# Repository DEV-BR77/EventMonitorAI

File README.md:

# EventMonitorAI

> **Lokale, datenschutzorientierte Plattform zur Erfassung, Analyse und lernenden Klassifizierung akustischer Ereignisse.**

EventMonitorAI verbindet ESP32-Audiosensoren, Raspberry-Pi-Edge-Verarbeitung, eine FastAPI-Ereignisplattform und **EventMonitor AudioLab** für historische Messungen. Ziel ist, große Mengen vorhandener und künftiger Lärmaufnahmen automatisch zu strukturieren, auffällige Abschnitte zu finden und durch bestätigte Zuordnungen schrittweise eine an die reale Umgebung angepasste Erkennung aufzubauen.

## Projektstatus

**Entwicklungsphase:** v1.0-Kandidat / Abnahme und Langzeittest

Aktuell vorhanden:

- ESP32-S3-Audiosender per UDP
- Raspberry-Pi-Empfänger mit YAMNet-basierter Klassifizierung
- FastAPI-Backend mit SQLite-Ereignisdatenbank
- REST-Endpunkte für Health-Check und Ereignisse
- geschütztes Dashboard mit Kalender, Timeline, Heatmap, Statistiken und Live-Ansicht
- lokale Benutzerrollen, Mehrgerätebetrieb, Live-Sound-Freigaben, installierbare PWA und Push-Benachrichtigungen
- Home-Assistant-Webhook und optionale PostgreSQL-Datenbank
- deutsche Label- und Kategoriezuordnung
- EventMonitor AudioLab für ZIP-Massenimport, Segmentierung, Anhören, Labeling und CSV-Export

Die Funktionen bis Phase 9 sind implementiert. Ein v1.0-Tag wird erst nach dem
dokumentierten 24-Stunden-Langzeittest, Restore-Test auf einer getrennten
Datenbank und der Betreiber-/Datenschutzfreigabe erstellt.

## Schwerpunkt der Erkennung

Das System wird zunächst für folgende akustische Klassen optimiert:

- Schreien und lautes Rufen
- Streit oder mehrere laute Stimmen
- Schlagen, Klopfen und andere Aufprallgeräusche
- Türknallen
- Auto und Vorbeifahrt
- Motorrad
- Hupe

Zusätzliche Negativ- und Kontextklassen wie normales Sprechen, Hund, Musik, Maschinen, Wind oder Regen reduzieren Fehlalarme.

> EventMonitorAI erkennt akustische Muster. Es stellt nicht zweifelsfrei fest, welche Person oder Ursache ein Geräusch erzeugt hat. Automatische Ergebnisse bleiben Vorschläge, bis sie bestätigt wurden.

## Systemübersicht

```text
ESP32-S3 + INMP441
        │ UDP-Audio
        ▼
Raspberry Pi / Edge Receiver
        │ Ereignisse + Pegel + Modellresultate + flüchtiger Live-Audiostream
        ▼
FastAPI Backend ───────────────► SQLite / später PostgreSQL
        │
        ├── REST API und geschütztes Dashboard
        ├── Live- und Ereignisdaten
        └── PostgreSQL, automatische Backups und Clips

Historische ZIP-/Audio-Messungen
        │
        ▼
EventMonitor AudioLab
        ├── Massenimport und Dublettenprüfung
        ├── dB-/Audio-Segmentierung
        ├── Human-in-the-Loop-Labeling
        └── Trainings- und Lärmprotokoll-Daten
```

Detaillierte Beschreibung: [docs/Architecture.md](docs/Architecture.md)

## Repository-Struktur

```text
EventMonitorAI/
├── .github/                 GitHub-Workflows und Vorlagen
├── backend/                 FastAPI-Backend und Datenmodell
├── edge/raspberry-pi/       Edge-Empfänger und lokale Klassifizierung
├── firmware/                ESP32-S3-Firmware
├── tools/audio-lab/         Historischer Import und Lernoberfläche
├── docs/                    Architektur, Betrieb, Entwicklung und Roadmap
├── tests/                   automatisierte Tests
├── scripts/                 Entwickler- und Prüfskripte
├── models/                  lokale Modellablage, Inhalte nicht versioniert
├── exports/                 lokale Exporte, Inhalte nicht versioniert
└── logs/                    lokale Logs, Inhalte nicht versioniert
```

## Schnellstart: Backend

Voraussetzungen: Python 3.11 oder neuer.

```powershell
cd backend
py -m venv .venv
.\.venv\Scripts\Activate.ps1
python -m pip install --upgrade pip
pip install -r requirements.txt
Copy-Item .env.example .env
uvicorn app.main:app --reload
```

Danach:

- API-Dokumentation: `http://127.0.0.1:8000/docs`
- Health-Check: `http://127.0.0.1:8000/health`
- Dashboard: `http://127.0.0.1:8000/`

Ausführliche Anleitung: [docs/getting-started/INSTALLATION.md](docs/getting-started/INSTALLATION.md)

## Schnellstart: EventMonitor AudioLab

```powershell
cd tools\audio-lab
.\start_windows.bat
```

AudioLab öffnet eine lokale Browseroberfläche für Import, Wiedergabe, Labeling und Auswertung. Details: [tools/audio-lab/README.md](tools/audio-lab/README.md)

## Entwicklung

Vor Änderungen bitte lesen:

- [CONTRIBUTING.md](CONTRIBUTING.md)
- [docs/development/CODING_GUIDELINES.md](docs/development/CODING_GUIDELINES.md)
- [docs/development/BRANCHING_AND_RELEASES.md](docs/development/BRANCHING_AND_RELEASES.md)
- [SECURITY.md](SECURITY.md)

Lokale Qualitätsprüfung:

```powershell
py scripts/check_project.py
```

Die GitHub-CI prüft Python-Syntax, Tests, sensible Dateien und grundlegende Repository-Hygiene.

## Dokumentation

| Thema | Dokument |
|---|---|
| Installation | [docs/getting-started/INSTALLATION.md](docs/getting-started/INSTALLATION.md) |
| Architektur | [docs/Architecture.md](docs/Architecture.md) |
| Dashboard und Integrationen | [docs/PHASE5_DASHBOARD.md](docs/PHASE5_DASHBOARD.md) |
| Zweistufige KI-Klassifikation | [docs/PHASE7_KI.md](docs/PHASE7_KI.md) |
| AudioLab | [tools/audio-lab/README.md](tools/audio-lab/README.md) |
| Roadmap | [docs/Roadmap.md](docs/Roadmap.md) |
| Produkt-Backlog | [docs/ProductBacklog.md](docs/ProductBacklog.md) |
| Entscheidungen | [docs/DecisionLog.md](docs/DecisionLog.md) und [docs/adr/](docs/adr/) |
| Betrieb und Datenschutz | [docs/operations/PRIVACY_AND_DATA.md](docs/operations/PRIVACY_AND_DATA.md) |
| Installation und Upgrade | [docs/operations/INSTALL_UPGRADE.md](docs/operations/INSTALL_UPGRADE.md) |
| Backup und Restore | [docs/operations/BACKUP_RESTORE.md](docs/operations/BACKUP_RESTORE.md) |
| Performance | [docs/operations/PERFORMANCE.md](docs/operations/PERFORMANCE.md) |
| Security-Review | [docs/operations/SECURITY_PRIVACY_REVIEW.md](docs/operations/SECURITY_PRIVACY_REVIEW.md) |
| v1.0-Kriterien | [docs/releases/V1_RELEASE_CRITERIA.md](docs/releases/V1_RELEASE_CRITERIA.md) |

## Leitprinzipien

1. **Privacy first** – lokale Verarbeitung und Datenkontrolle.
2. **Local first** – Kernfunktionen ohne Cloud-Zwang.
3. **Everything is an event** – ein gemeinsames Ereignismodell.
4. **Human in the loop** – bestätigte Labels statt blindem Selbstlernen.
5. **Simple before clever** – nachvollziehbare, testbare Schritte.
6. **Documentation matters** – Architektur und Entscheidungen werden dokumentiert.
7. **Quality over speed** – stabile Daten und reproduzierbare Ergebnisse.

## Lizenz

Siehe [LICENSE](LICENSE).

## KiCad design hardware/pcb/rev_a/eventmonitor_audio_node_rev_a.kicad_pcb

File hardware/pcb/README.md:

# JLCPCB-Kalkulationspakete

`generated/carrier/eventmonitor_audio_carrier-JLCPCB.zip` ist ein zweilagiger,
gerouteter Rev-A-Prototyp fuer das Freenove ESP32-S3 N16R8 Board und einen
INMP441-Stecksockel. Vor Bestellung sind die tatsaechlichen Header-Mittelpunkte
und die Pinreihenfolge des gekauften Mikrofons mit dem Messschieber zu pruefen.

Die beiden SMD-Verzeichnisse sind Preisvorlagen mit finaler Umrissgroesse, BOM und
CPL-Schema. Sie sind **nicht** als Fertigungsfreigabe gedacht: USB-C, ESD,
Stromversorgung, Antennen-Freihaltezone sowie bei LiPo die Schutz- und
Ladeschaltung werden erst nach Auswahl des konkreten Akkus final geroutet.

## Native-USB-SMD-Platine mit externer Antenne (Kalkulation)

`generated/smd_native_usb_external_antenna_quote/` enthält die aktuelle
Kalkulationsmappe ohne Steckfassungen:

- `smd_native_usb_external_antenna_quote-JLCPCB.zip` – Gerberarchiv für den
  PCB-Preisrechner;
- `BOM.csv` – Stückliste einschließlich Montagehinweisen;
- `CPL.csv` – Bestückungskoordinaten für JLCPCB;
- `board-preview.png` – reine Sichtprüfung der Bauteilplatzierung.

Die Platine ist 65 × 50 mm groß und enthält das externe-Antennenmodul
`ESP32-S3-WROOM-1U-N16R8`, einen direkt aufgelöteten ICS-43434-I²S-MEMS-Sensor,
USB-C für 5 V und natives USB (GPIO19/GPIO20), AMS1117-3.3, BOOT/RESET,
Status-LED und vier M2.5-Gehäusebohrungen. Das RP-SMA-Teil ist bewusst kein
Platinenbauteil: Es ist ein U.FL-auf-RP-SMA-Bulkhead-Pigtail, das direkt an die
bereits vorhandene U.FL-Buchse des WROOM-1U-Moduls kommt und später im Gehäuse
verschraubt wird.

Wichtig: `ESP32-S3-WROOM-1-N16R8-H4` ist keine einzelne Espressif-Variante.
`N16R8` (16 MB Flash, 8 MB PSRAM) und `H4` sind unterschiedliche
Speicher-/Temperaturvarianten. Für die gewünschte RP-SMA-Antenne ist die
`1U`-Variante erforderlich. Diese Mappe ist absichtlich als **QUOTE ONLY –
NOT FOR MANUFACTURING** angelegt: Vor einer Fertigungsfreigabe fehlen noch
Schaltplan/Netzliste, USB-ESD-Schutz, vierlagiges Impedanz- und RF-Routing,
Mikrofon-Akustiköffnung sowie DRC/ERC und ein Musteraufbau.

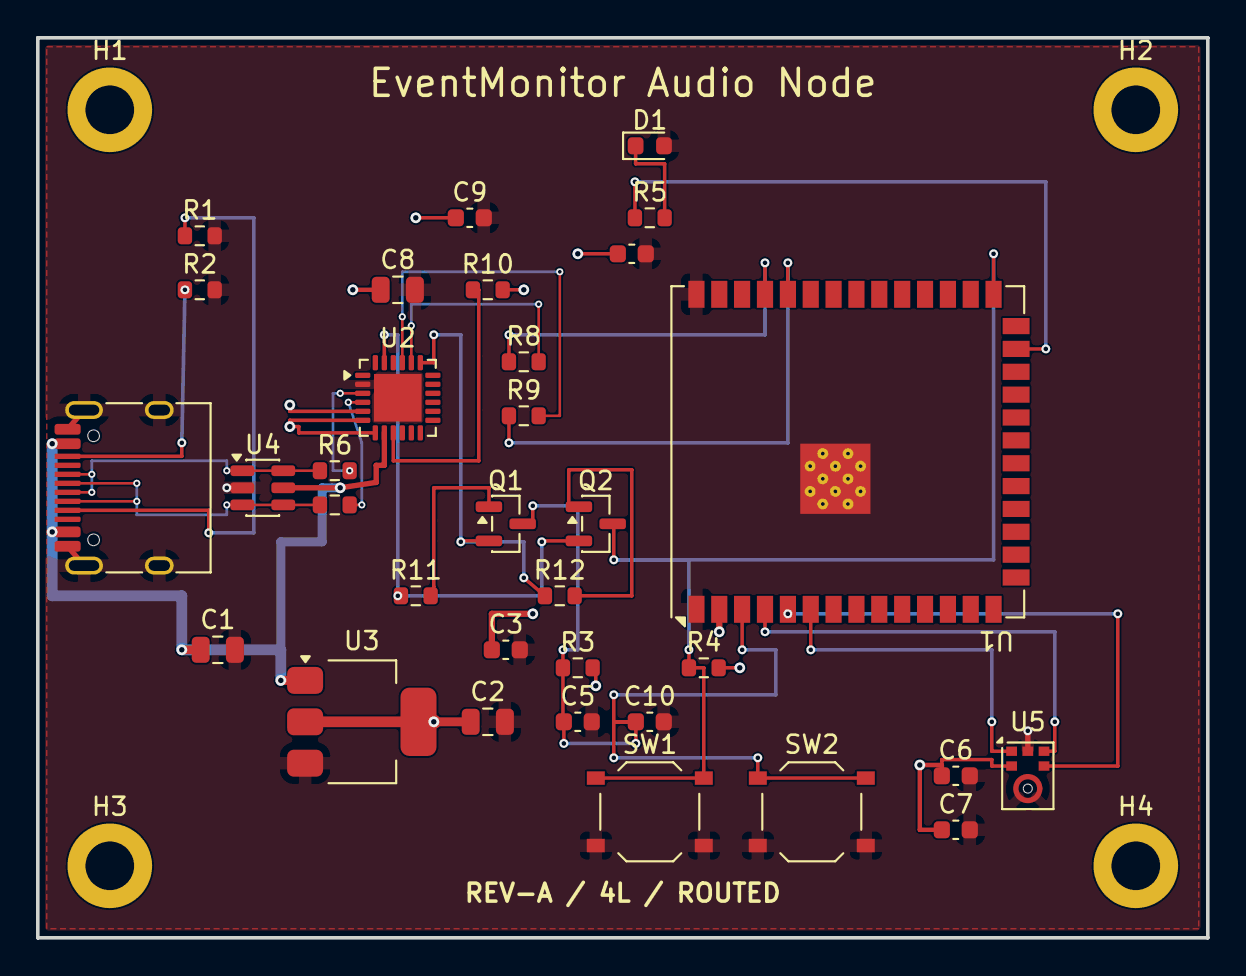
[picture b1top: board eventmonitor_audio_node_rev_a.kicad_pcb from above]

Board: 4 copper layers, 65.0 x 50.0 mm, 37 parts (0 on the bottom side), 25 nets.

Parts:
C1: 10u VIN; C_0805_2012Metric
C2: 10u VOUT; C_0805_2012Metric
C3: 100n U3; C_0603_1608Metric
C4: 100n U1; C_0603_1608Metric
C5: 100n EN; C_0603_1608Metric
C6: 1u MIC; C_0603_1608Metric
C7: 100n MIC; C_0603_1608Metric
C8: 4u7 U2; C_0805_2012Metric
C9: 100n U2; C_0603_1608Metric
C10: 1u EN; C_0603_1608Metric
D1: GREEN; LED_0603_1608Metric
H1, H2, H3, H4: M2.5; MountingHole_2.7mm_M2.5_DIN965_Pad
J1: USB-C USB2.0; USB_C_Receptacle_HRO_TYPE-C-31-M-12
Q1, Q2: BC847B; SOT-23
R1, R2: 5.1k; R_0603_1608Metric
R3: 10k EN; R_0603_1608Metric
R4: 10k BOOT; R_0603_1608Metric
R5: 1k LED; R_0603_1608Metric
R6: 22R D+; R_0603_1608Metric
R7: 22R D-; R_0603_1608Metric
R8: 499R TX; R_0603_1608Metric
R9: 499R RX; R_0603_1608Metric
R10: 1k U2 RST; R_0603_1608Metric
R11: 10k DTR; R_0603_1608Metric
R12: 10k RTS; R_0603_1608Metric
SW1: BOOT; SW_Push_1P1T_XKB_TS-1187A
SW2: RESET; SW_Push_1P1T_XKB_TS-1187A
U1: ESP32-S3-WROOM-1U-N16R8; ESP32-S3-WROOM-1U
U2: CP2102N-A02-GQFN24R; QFN-24-1EP_4x4mm_P0.5mm_EP2.65x2.65mm
U3: AMS1117-3.3; SOT-223-3_TabPin2
U4: USBLC6-2SC6; SOT-23-6
U5: ICS-43434; InvenSense_ICS-43434-6_3.5x2.65mm

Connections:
+3V3: C2.1, C3.1, C4.1, C6.1, C7.1, C8.1, C9.1, R3.2, R4.2, R10.2, U1.2, U2.5, U2.6, U2.7, U3.2, U5.2
AUTO_DTR: Q2.2, R11.1, U2.23
AUTO_RTS: Q1.2, R12.1, U2.19
BOOT: Q2.3, R4.1, SW1.1, U1.27
EN: C5.1, C10.1, Q1.3, R3.1, SW2.1, U1.3
GND: C1.2, C2.2, C3.2, C4.2, C5.2, C6.2, C7.2, C8.2, C9.2, C10.2, D1.2, J1.A1, J1.A12, J1.B1, J1.B12, J1.SH, R1.2, R2.2, SW1.2, SW2.2, U1.1, U1.40, U1.41, U2.2, U2.25, U3.3, U4.2, U5.3, U5.6
I2S_BCLK: U1.5, U5.4
I2S_DATA: U1.6, U5.1
I2S_WS: U1.4, U5.5
LED_A: D1.1, R5.2
LED_STATUS: R5.1, U1.25
Q1_BASE: Q1.1, R11.2
Q2_BASE: Q2.1, R12.2
U2_RST: R10.1, U2.9
UART_RX_CP: R8.2, U2.20
UART_RX_ESP: R9.1, U1.36
UART_TX_CP: R9.2, U2.21
UART_TX_ESP: R8.1, U1.37
USB_5V: C1.1, J1.A4, J1.A9, J1.B4, J1.B9, U2.8, U3.1, U4.5
USB_CC1: J1.A5, R1.1
USB_CC2: J1.B5, R2.1
USB_D+: R6.2, U2.3
USB_D+_ESD: J1.A6, J1.B6, R6.1, U4.1, U4.6
USB_D-: R7.2, U2.4
USB_D-_ESD: J1.A7, J1.B7, R7.1, U4.3, U4.4

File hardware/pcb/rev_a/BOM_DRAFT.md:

# Rev-A preliminary BOM

| References | Part / value | Package | Role |
| --- | --- | --- | --- |
| U1 | ESP32-S3-WROOM-1U-N16R8 | module | MCU and external U.FL antenna connector |
| U2 | CP2102N-A02-GQFN24R (`C969151`) | QFN-24-EP 4×4 mm | USB-to-UART programming bridge; includes DTR and RTS for standard auto-programming |
| U3 | AMS1117-3.3 | SOT-223-3 | 5 V to 3.3 V regulator |
| U4 | USBLC6-2SC6 | SOT-23-6 | USB ESD protection |
| U5 | ICS-43434 | LGA-6 | bottom-port I²S microphone |
| J1 | USB-C USB2.0 receptacle | 16-pin SMD | power and data |
| SW1 / SW2 | SMD tactile switch | 3×4 mm | BOOT / RESET |
| Q1 / Q2 | BC847B | SOT-23 | auto-programming pair |
| D1 | green LED | 0603 | status output |
| R1 / R2 | 5.1 kΩ 1% | 0603 | USB-C CC pull-downs |
| R3 / R4 | 10 kΩ 1% | 0603 | EN and GPIO0 pull-ups |
| R5 | 1 kΩ | 0603 | LED resistor |
| R6 / R7 | 22 Ω | 0603 | optional USB damping |
| R8 / R9 | 499 Ω | 0603 | UART series resistors |
| R11 / R12 | 10 kΩ 1% | 0603 | DTR/RTS auto-program base resistors |
| R10 | 1 kΩ | 0603 | CP2102N reset pull-up |
| C1 | 10 µF 10 V X5R | 0805 | AMS1117 input |
| C2 | 10 µF 6.3 V X5R | 0805 | AMS1117 output |
| C3 / C4 | 100 nF X7R | 0603 | regulator / MCU bypass |
| C5 | 100 nF X7R | 0603 | EN reset capacitor |
| C6 | 1 µF X7R | 0603 | microphone bypass |
| C7 | 100 nF X7R | 0603 | microphone bypass |
| C8 | 4.7 µF 6.3 V X5R | 0805 | CP2102N VDD/VIO bypass |
| C9 | 100 nF X7R | 0603 | CP2102N local bypass |
| C10 | 1 µF X7R | 0603 | EN auto-program reset timing capacitor |
| H1–H4 | M2.5, 2.7 mm NPTH | PCB | enclosure mounting |
| P1 | U.FL-to-RP-SMA bulkhead pigtail | cable | user supplied; attaches directly to U1 |

Confirmed at the design check: U1 is LCSC `C3013946`, U2 is `C969151`, and U5
is `C5656610`. Every remaining row still requires a currently available
LCSC/JLC part number and footprint check before the PCBA BOM is exported. The
machine-readable draft is kept locally as `BOM_DRAFT.csv`; generated fabrication
BOM/CPL archives remain untracked until the design has passed review.

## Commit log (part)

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2026-06-29 Initial NoiseMonitorAI foundation
